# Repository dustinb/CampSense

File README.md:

# Camp Sense

**Battery energy monitoring and weather app with ESP32 hardware**

The Camp Sense app connects to the WattIsIt ESP32 hardware module via Bluetooth and displays battery energy usage and weather data.

## 🚀 Quick Start

- **📱 [Download App](https://apps.apple.com/us/app/camp-sense/id6741625671)** - Available on the App Store
- **🌐 [View Website](https://campsense.app)** - Full documentation and hardware details

## 📁 Repository Structure

- `App/` - React Native mobile app (Expo)
- `Arduino/` - ESP32 firmware sketch
- `v1.kicad_pro` - KiCad project

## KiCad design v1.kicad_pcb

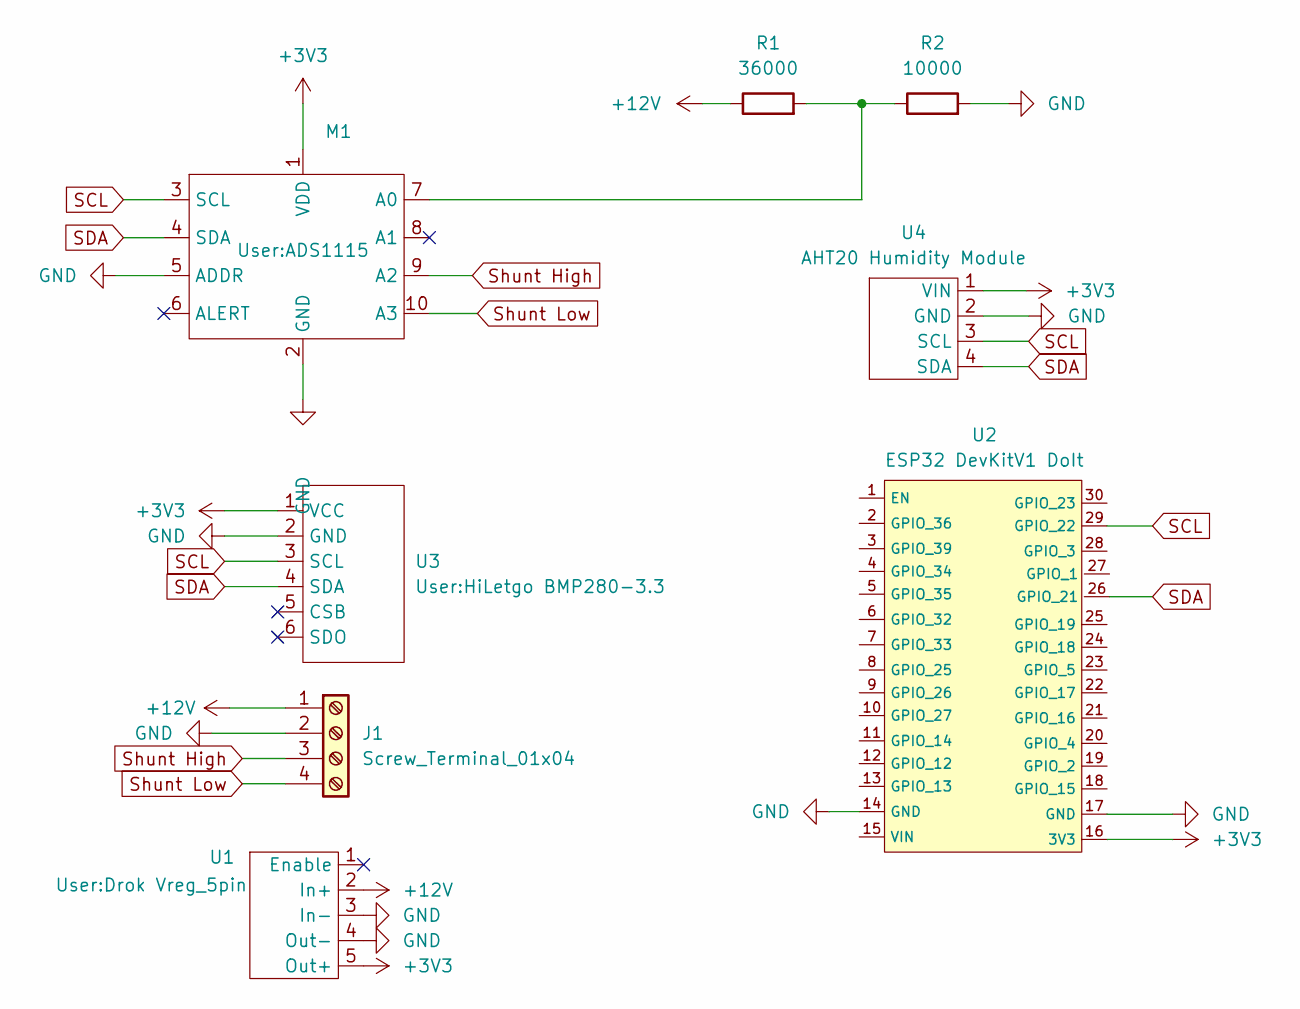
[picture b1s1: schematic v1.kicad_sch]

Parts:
J1: Screw_Terminal_01x04; Screw Terminal 2.54 x4
M1: ADS1115
R1: 36000; R_Axial_DIN0207_L6.3mm_D2.5mm_P10.16mm_Horizontal
R2: 10000; R_Axial_DIN0207_L6.3mm_D2.5mm_P10.16mm_Horizontal
U1: Drok Vreg_5pin
U2: ESP32 DevKitV1 DoIt
U3: HiLetgo BMP280-3.3
U4: AHT20 Humidity Module

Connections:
+3V3: M1.1 (VDD), U1.5 (Out+), U2.16 (3V3), U3.1 (VCC), U4.1 (VIN)
+12V: J1.1, R1.1, U1.2 (In+)
GND: J1.2, M1.2 (GND), M1.5 (ADDR), R2.2, U1.3 (In-), U1.4 (Out-), U2.14 (GND), U2.17 (GND), U3.2 (GND), U4.2 (GND)
unnamed: M1.7 (A0), R1.2, R2.1
SCL: M1.3 (SCL), U2.29 (GPIO_22), U3.3 (SCL), U4.3 (SCL)
SDA: M1.4 (SDA), U2.26 (GPIO_21), U3.4 (SDA), U4.4 (SDA)
Shunt High: J1.3, M1.9 (A2)
Shunt Low: J1.4, M1.10 (A3)

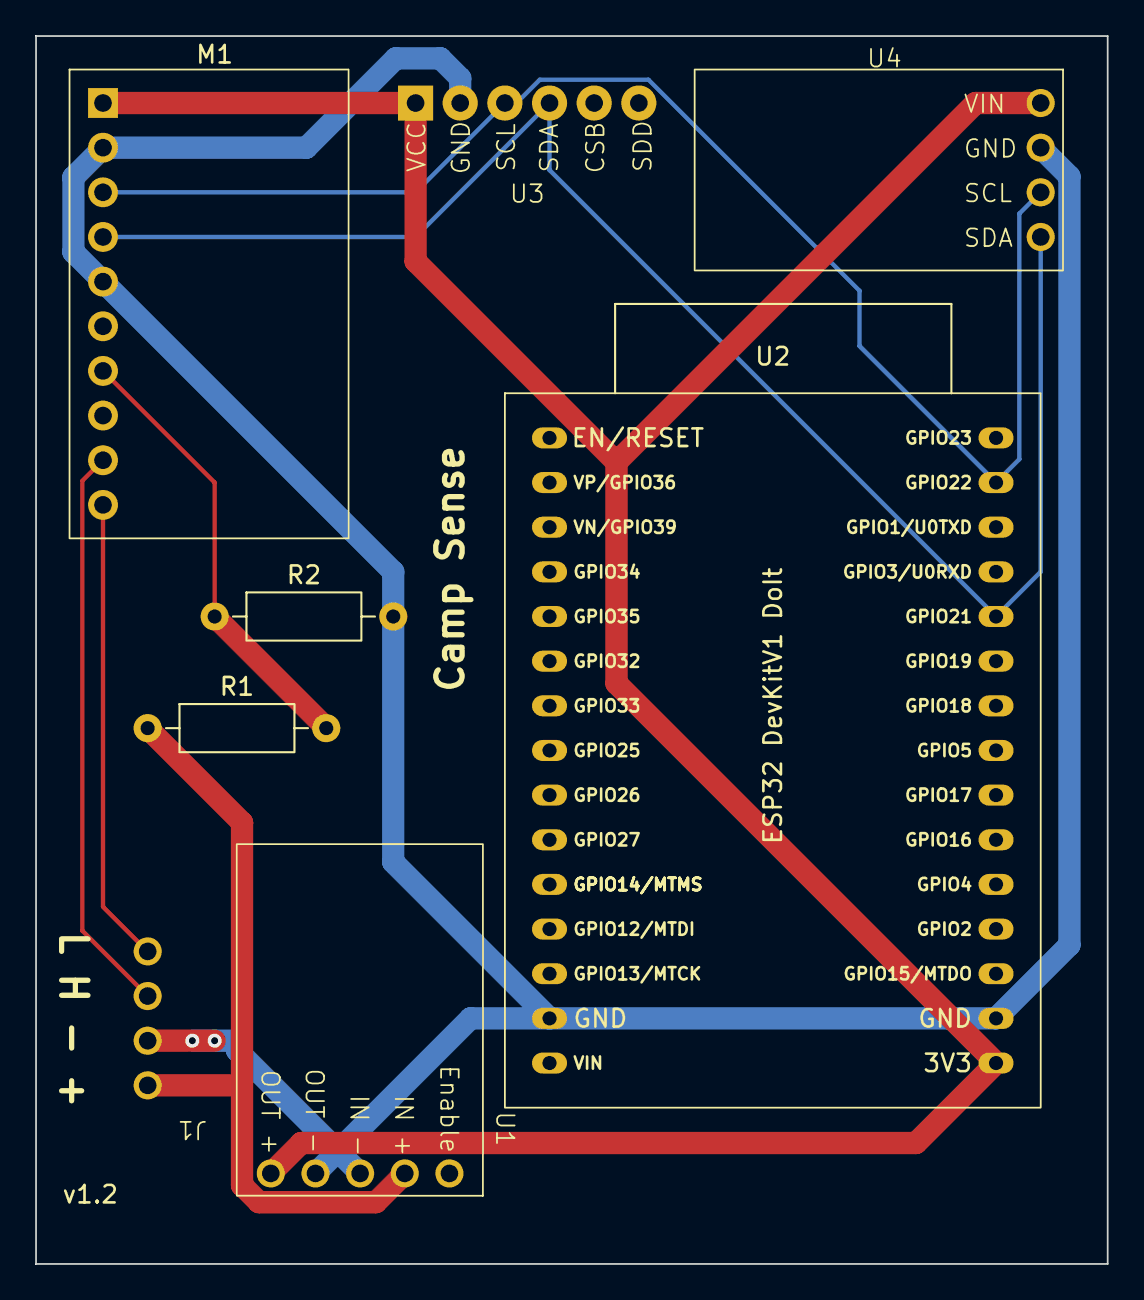
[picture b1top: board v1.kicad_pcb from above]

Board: 2 copper layers, 61.0 x 69.8 mm, 8 parts (0 on the bottom side), 8 nets.

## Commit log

2025-04-17 Expo SDK to 52 for issue with newer xCode versions. Install notes
2025-04-17 .env.example
2025-04-17 Icon
2025-05-03 Provide longer description and app notes
2025-05-03 Move remoteXY note
2025-07-14 ios build configs.
2025-08-28 Moved from platform.io to Arduino IDE
2025-09-04 Update build number. Added privacy policy
2025-09-04 Remove main title
2025-09-04 Update BOM links
2025-09-11 Update purpose strings (review feedback). bump build #
2025-09-14 Website layout
2025-09-18 Working on alternave voltage converter
2025-10-23 Version 1.2 pcb, 3.3 volt adc, updated step down
2025-11-04 Add case files
2025-11-15 Expo 52 -> 54. Android support
